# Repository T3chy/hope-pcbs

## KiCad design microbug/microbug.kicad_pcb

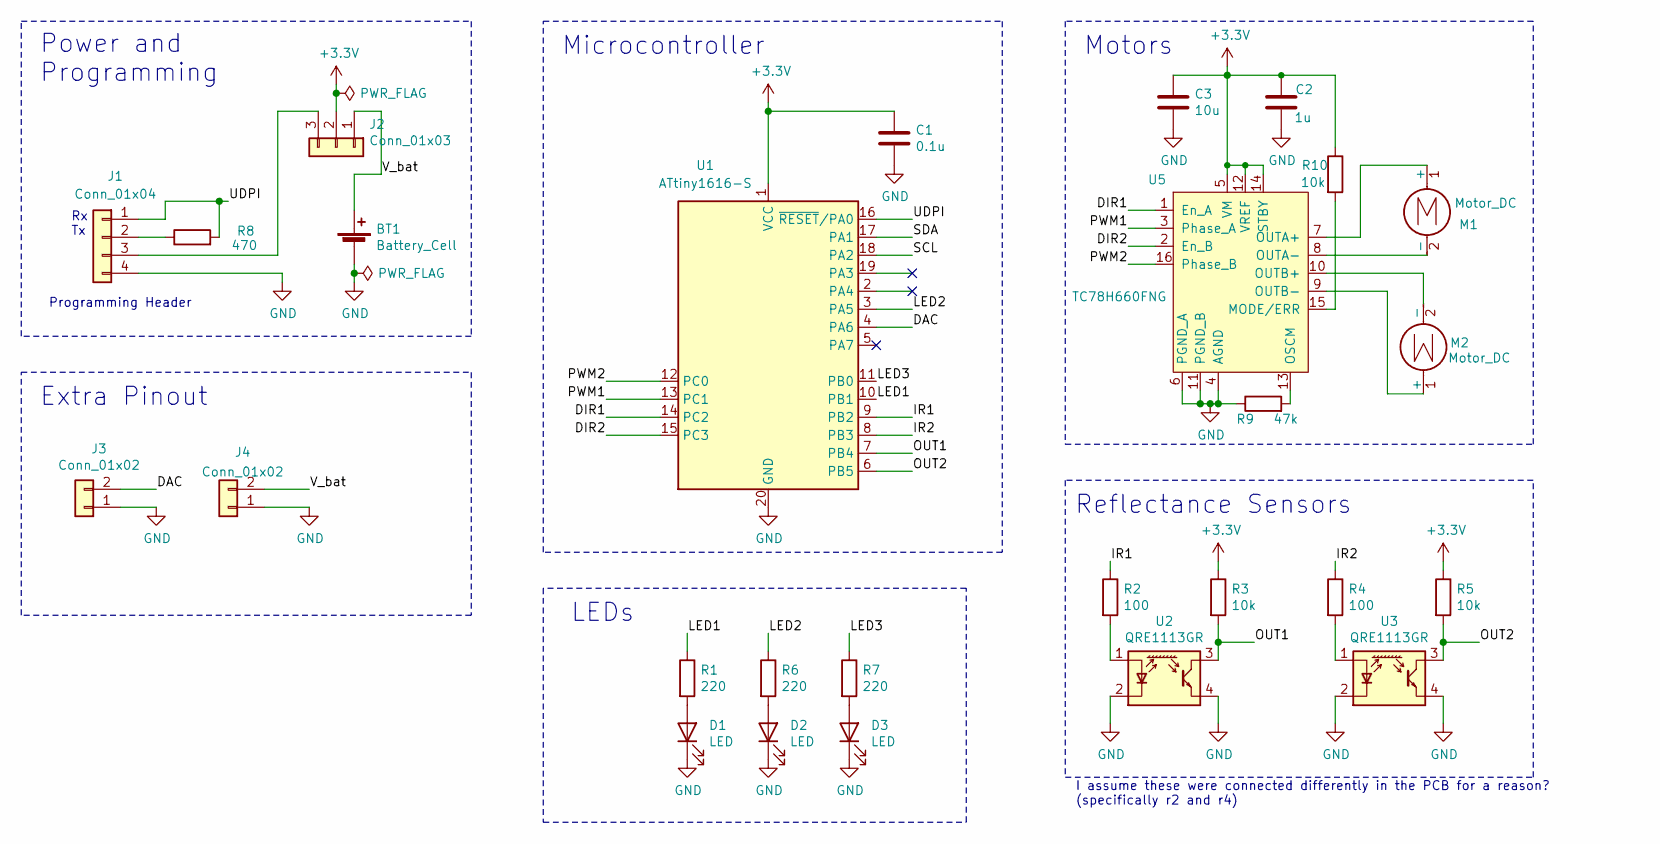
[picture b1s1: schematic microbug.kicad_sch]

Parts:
BT1: Battery_Cell; BK-883
C1: 0.1u; C_0603_1608Metric_Pad1.05x0.95mm_HandSolder
C2: 1u; C_0603_1608Metric_Pad1.05x0.95mm_HandSolder
C3: 10u; C_0603_1608Metric_Pad1.05x0.95mm_HandSolder
D1, D2, D3: LED; LED_D3.0mm
J1: Conn_01x04; PinHeader_1x04_P2.54mm_Vertical
J2: Conn_01x03; PinHeader_1x03_P2.54mm_Vertical
J3, J4: Conn_01x02; PinHeader_1x02_P2.54mm_Vertical
M1, M2: Motor_DC; micro_motor_5mm
R1, R6, R7: 220; R_0603_1608Metric_Pad1.05x0.95mm_HandSolder
R2, R4: 100; R_0603_1608Metric_Pad1.05x0.95mm_HandSolder
R3, R5, R10: 10k; R_0603_1608Metric_Pad1.05x0.95mm_HandSolder
R8: 470; R_0603_1608Metric_Pad1.05x0.95mm_HandSolder
R9: 47k; R_0603_1608Metric_Pad1.05x0.95mm_HandSolder
U1: ATtiny1616-S; SOIC-20W_7.5x12.8mm_P1.27mm
U2, U3: QRE1113GR; OnSemi_CASE100CY
U5: TC78H660FNG; TSSOP-16_4.4x5mm_P0.65mm

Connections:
+3V3: C1.1, C2.1, C3.1, J2.2, R3.1, R5.1, R10.1, U1.1 (VCC), U5.5 (VM), U5.12 (VREF), U5.14 (STBY)
/DAC: J3.2, U1.4 (PA6)
/DIR1: U1.14 (PC2), U5.1 (En_A)
/DIR2: U1.15 (PC3), U5.2 (En_B)
/IR1: R2.1, U1.9 (PB2)
/IR2: R4.1, U1.8 (PB3)
/LED1: R1.1, U1.10 (PB1)
/LED2: R6.1, U1.3 (PA5)
/LED3: R7.1, U1.11 (PB0)
/OUT1: R3.2, U1.7 (PB4), U2.3
/OUT2: R5.2, U1.6 (PB5), U3.3
/PWM1: U1.13 (PC1), U5.3 (Phase_A)
/PWM2: U1.12 (PC0), U5.16 (Phase_B)
/SCL: U1.18 (PA2)
/SDA: U1.17 (PA1)
/UDPI: J1.1, R8.2, U1.16 (~RESET/PA0)
/V_bat: BT1.1 (+), J2.1, J4.2
GND: BT1.2 (-), C1.2, C2.2, C3.2, D1.1 (K), D2.1 (K), D3.1 (K), J1.4, J3.1, J4.1, R9.1, U1.20 (GND), U2.2 (K), U2.4, U3.2 (K), U3.4, U5.4 (AGND), U5.6 (PGND_A), U5.11 (PGND_B)
unnamed: D1.2 (A), R1.2
unnamed: D2.2 (A), R6.2
unnamed: D3.2 (A), R7.2
unnamed: J1.2, R8.1
unnamed: J1.3, J2.3
unnamed: M1.1 (+), U5.7 (OUTA+)
unnamed: M1.2 (-), U5.8 (OUTA-)
unnamed: M2.1 (+), U5.9 (OUTB-)
unnamed: M2.2 (-), U5.10 (OUTB+)
unnamed: R2.2, U2.1 (A)
unnamed: R4.2, U3.1 (A)
unnamed: R9.2, U5.13 (OSCM)
unnamed: R10.2, U5.15 (MODE/ERR)

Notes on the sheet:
Power and Programming
Extra Pinout
Programming Header
Rx Tx
Microcontroller
LEDs
Reflectance Sensors
I assume these were connected differently in the PCB for a reason? (specifically r2 and r4)
Motors

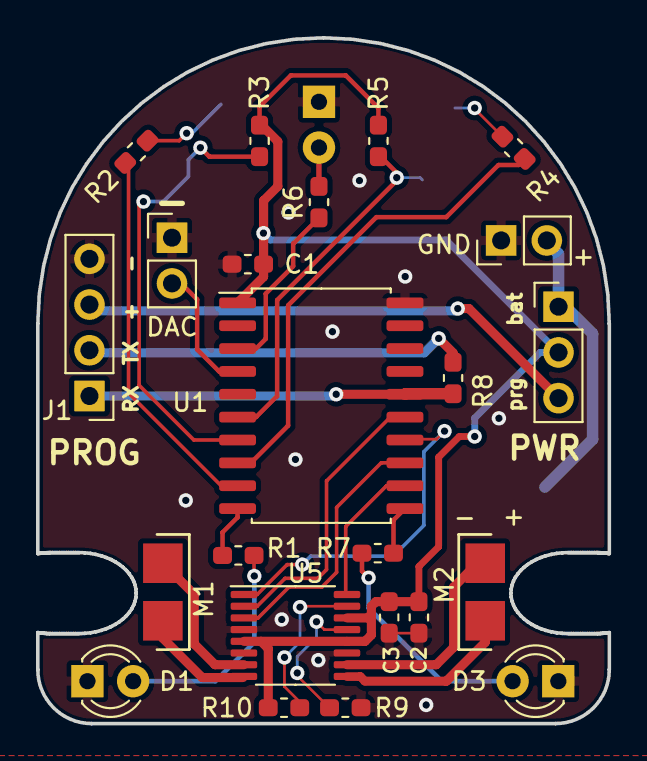
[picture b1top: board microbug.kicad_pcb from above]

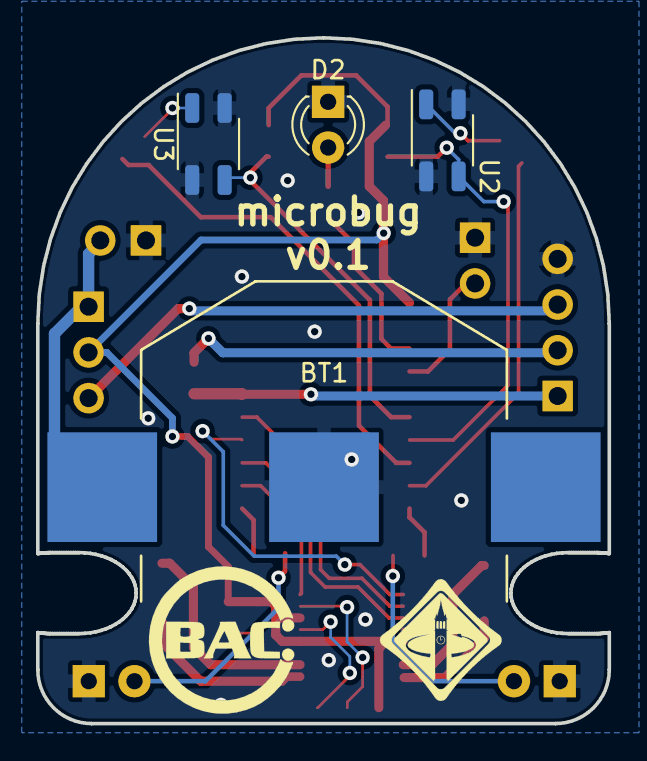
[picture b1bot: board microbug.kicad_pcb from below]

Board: 2 copper layers, 31.7 x 38.1 mm, 27 parts (4 on the bottom side), 29 nets.

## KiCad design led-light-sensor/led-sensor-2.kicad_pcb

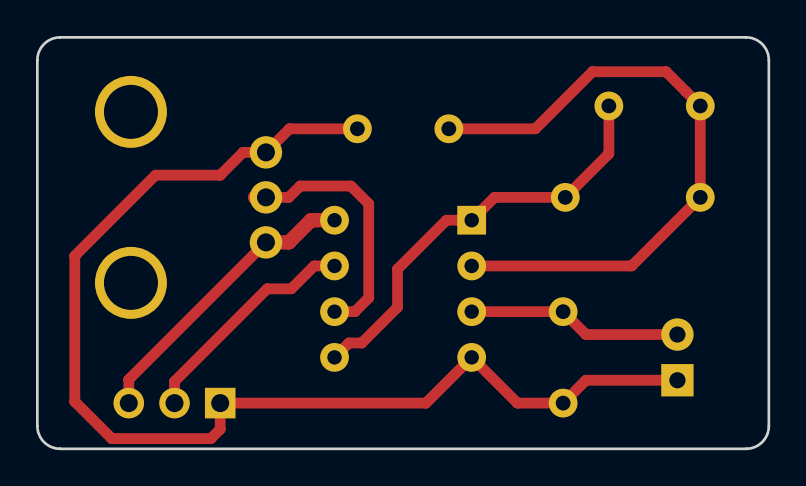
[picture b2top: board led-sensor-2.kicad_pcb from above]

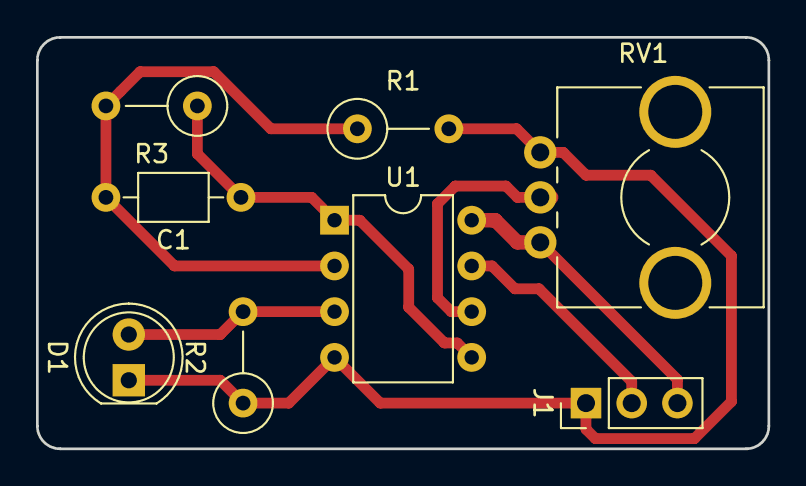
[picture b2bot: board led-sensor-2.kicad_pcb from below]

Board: 2 copper layers, 40.6 x 22.9 mm, 8 parts (8 on the bottom side), 7 nets.

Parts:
C1: 1u; C_Axial_L3.8mm_D2.6mm_P7.50mm_Horizontal
D1: LED; LED_D5.0mm
J1: CONN_01X03; Pin_Header_Straight_1x03_Pitch2.54mm
R1: 1k; R_Axial_DIN0309_L9.0mm_D3.2mm_P5.08mm_Vertical
R2: 1M; R_Axial_DIN0309_L9.0mm_D3.2mm_P5.08mm_Vertical
R3: 47k; R_Axial_DIN0309_L9.0mm_D3.2mm_P5.08mm_Vertical
RV1: POT; Potentiometer_Alps_RK09L_Sleve_Single_Horizontal
U1: LMC6482; DIP-8_W7.62mm

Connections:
+3V3: J1.3, RV1.1, U1.8
/Vout: J1.2, U1.7
GND: D1.1, J1.1, R1.2, R2.1, RV1.3, U1.4
unnamed: C1.1, R3.1, U1.1, U1.5
unnamed: C1.2, R1.1, R3.2, U1.2
unnamed: D1.2, R2.2, U1.3
unnamed: RV1.2, U1.6

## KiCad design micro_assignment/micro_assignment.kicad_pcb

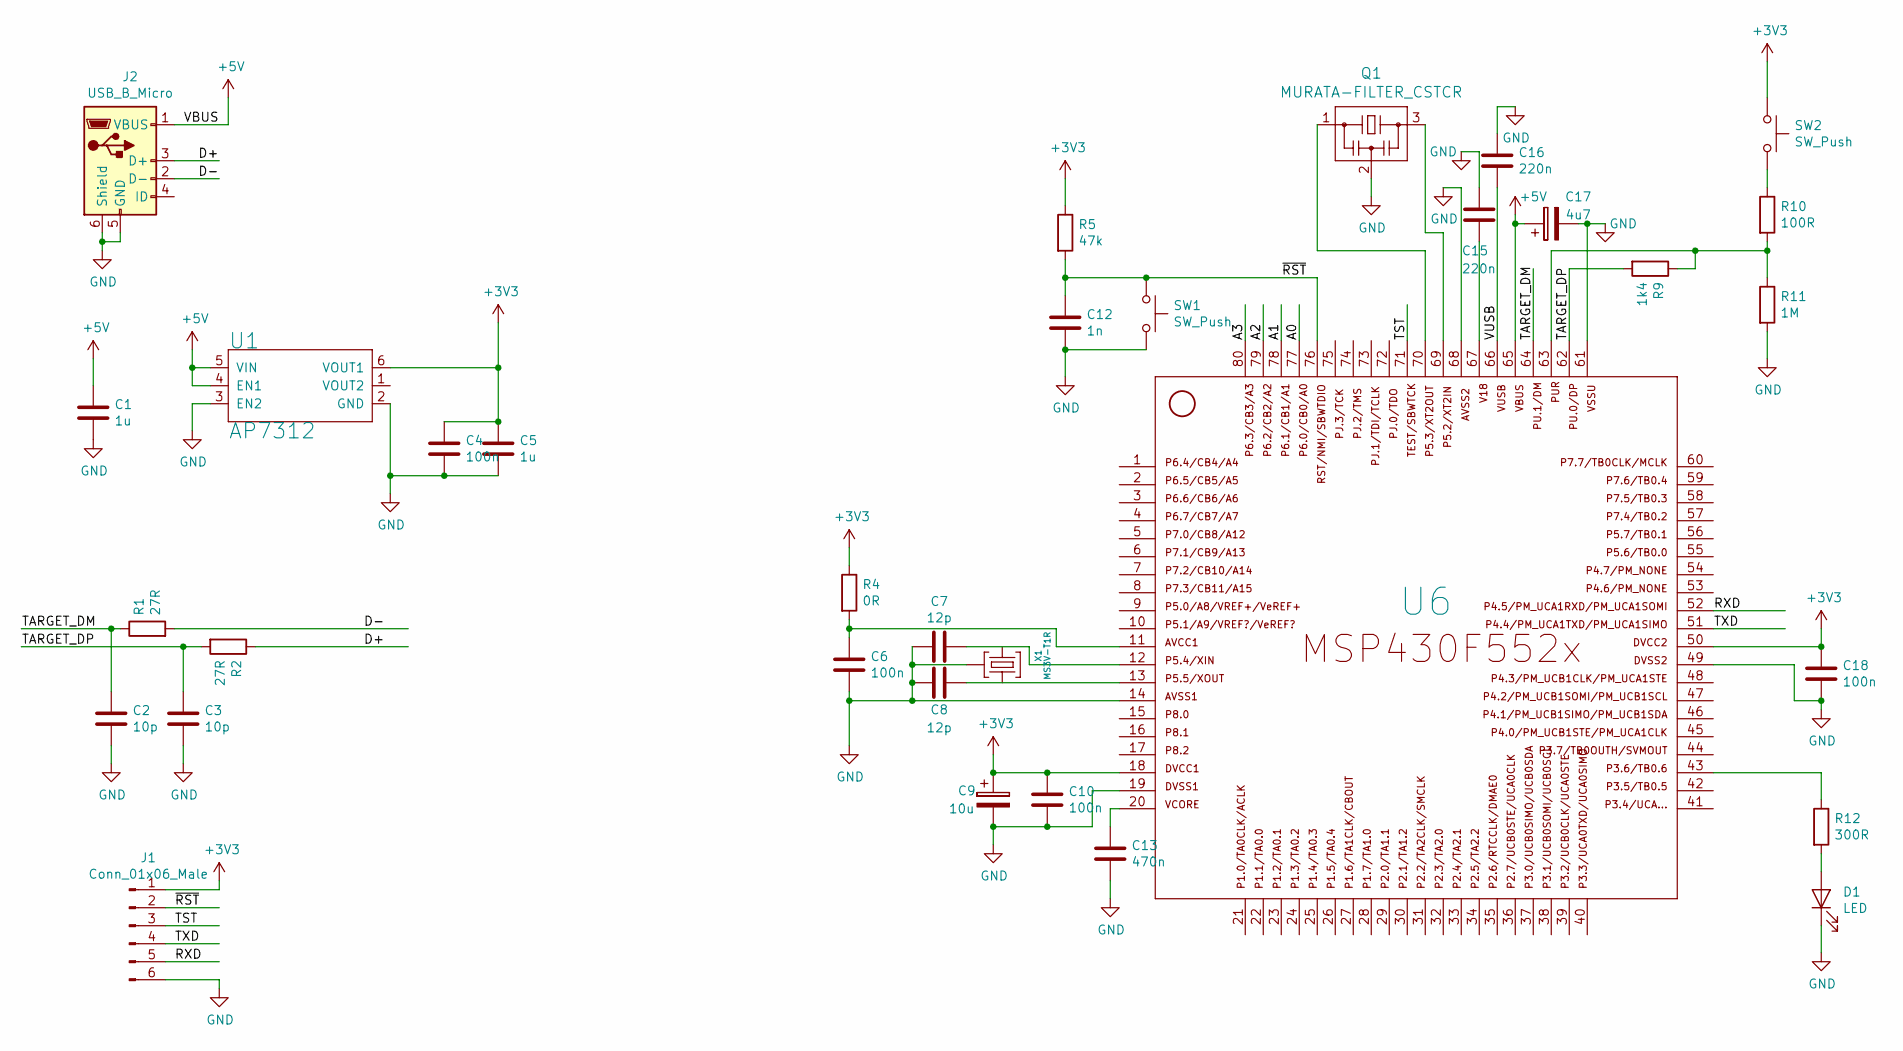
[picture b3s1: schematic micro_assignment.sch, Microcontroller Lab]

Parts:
C1, C5: 1u; C_0805_2012Metric_Pad1.15x1.40mm_HandSolder
C2, C3: 10p; C_0402_1005Metric
C4, C6, C10, C18: 100n; C_0805_2012Metric_Pad1.15x1.40mm_HandSolder
C7, C8: 12p; C_0805_2012Metric_Pad1.15x1.40mm_HandSolder
C9: 10u; 153CLV-0405
C12: 1n; C_0805_2012Metric_Pad1.15x1.40mm_HandSolder
C13: 470n; C_0805_2012Metric_Pad1.15x1.40mm_HandSolder
C15, C16: 220n; C_0805_2012Metric_Pad1.15x1.40mm_HandSolder
C17: 4u7; C_SMD_WURTH_865080540002
D1: LED; LED_0805_2012Metric_Pad1.15x1.40mm_HandSolder
J1: Conn_01x06_Male; PinHeader_1x06_P2.54mm_Vertical
J2: USB_B_Micro; USB_Micro-B_Molex-105017-0001
Q1: MURATA-FILTER_CSTCR; MURATA-CSTCR_G
R1, R2: 27R; R_0402_1005Metric
R4: 0R; R_0805_2012Metric_Pad1.15x1.40mm_HandSolder
R5: 47k; R_0805_2012Metric_Pad1.15x1.40mm_HandSolder
R9: 1k4; R_0805_2012Metric_Pad1.15x1.40mm_HandSolder
R10: 100R; R_0805_2012Metric_Pad1.15x1.40mm_HandSolder
R11: 1M; R_0805_2012Metric_Pad1.15x1.40mm_HandSolder
R12: 300R; R_0805_2012Metric_Pad1.15x1.40mm_HandSolder
SW1, SW2: SW_Push; SW_PUSH_6mm
U1: AP7312; SOT26
U6: F552X---PN80; LQFP-80_12x12mm_P0.5mm
X1: MS3V-T1R

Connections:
+3V3: C4.1, C5.1, C9.1, C10.1, C18.1, J1.1, R4.1, R5.1, SW2.1, U1.6 (VOUT1), U6.18, U6.50
+5V: C1.1, C17.1, J2.1 (VBUS), U1.4 (EN1), U1.5 (VIN), U6.65
/A0: U6.77
/A1: U6.78
/A2: U6.79
/A3: U6.80
/D+: J2.3 (D+), R2.1
/D-: J2.2 (D-), R1.2
/RXD: J1.5, U6.52
/TARGET_DM: C2.1, R1.1, U6.64
/TARGET_DP: C3.1, R2.2, R9.2, U6.62
/TST: J1.3, U6.71
/TXD: J1.4, U6.51
/VUSB: C16.2, U6.66
/~RST: C12.1, J1.2, R5.2, SW1.1, U6.76
GND: C1.2, C2.2, C3.2, C4.2, C5.2, C6.2, C7.2, C8.2, C9.2, C10.2, C12.2, C13.1, C15.1, C16.1, C17.2, C18.2, D1.1 (K), J1.6, J2.5 (GND), J2.6 (Shield), Q1.2, R11.2, SW1.2, U1.2 (GND), U1.3 (EN2), U6.14, U6.19, U6.49, U6.61, U6.68, X1.3 (GND)
unnamed: C6.1, R4.2, U6.11
unnamed: C7.1, U6.12
unnamed: C8.1, U6.13
unnamed: C13.2, U6.20
unnamed: C15.2, U6.67
unnamed: D1.2 (A), R12.2
unnamed: Q1.1, U6.70
unnamed: Q1.3, U6.69
unnamed: R10.1, SW2.2
unnamed: R9.1, R10.2, R11.1, U6.63
unnamed: R12.1, U6.43

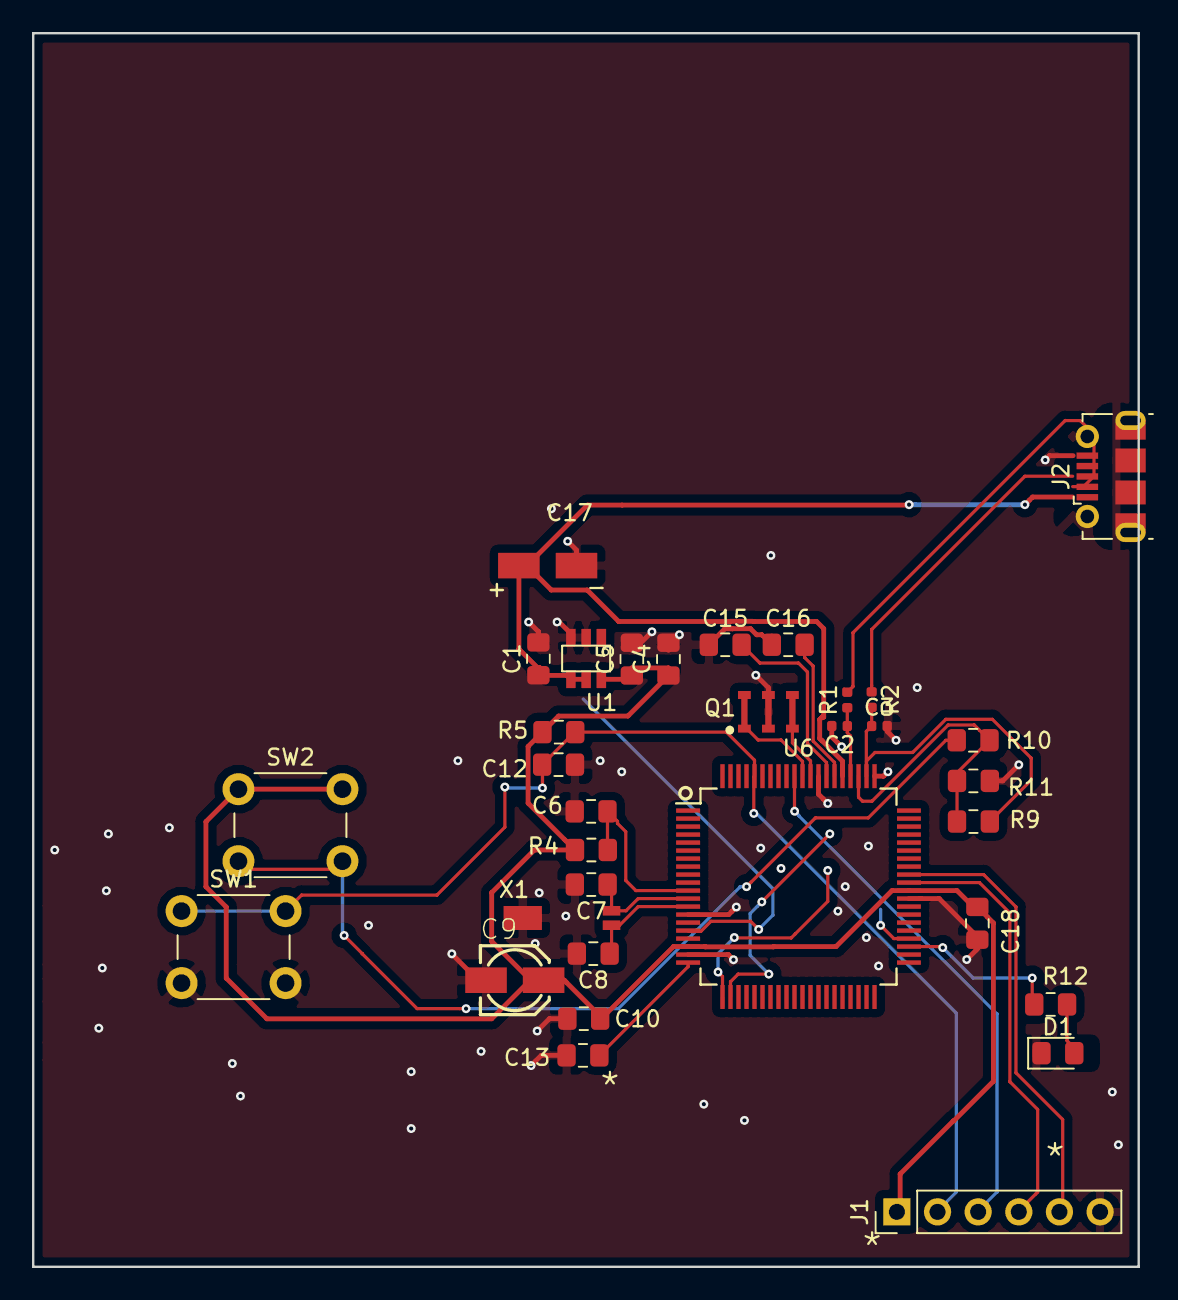
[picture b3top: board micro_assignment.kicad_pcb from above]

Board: 2 copper layers, 69.1 x 77.1 mm, 33 parts (0 on the bottom side), 23 nets.

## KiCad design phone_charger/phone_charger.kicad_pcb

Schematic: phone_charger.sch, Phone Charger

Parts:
C1: 10u (25V); C_1206_3216Metric_Pad1.42x1.75mm_HandSolder; MPN GRM319R61E106KA12D; Digi-Key_PN 490-5525-1-ND
C2: 0.1u (6.3V); C_0603_1608Metric_Pad1.05x0.95mm_HandSolder; MPN ECJ-1V1C104K
C3, C4: 22u (16V); C_0805_2012Metric_Pad1.15x1.40mm_HandSolder; MPN GRM21BR61C226ME44L; Digi-Key_PN 490-10747-1-ND
D1: LED; LED_D3.0mm; MPN 151034RS03000; Digi-Key_PN 732-11403-ND
D2: D_Schottky; D_SOD-123H; MPN CDBMT240-HF; Digi-Key_PN 641-1446-1-ND
D3: B330B; D_SMB_Handsoldering; MPN B330B-13-F; Digi-Key_PN 621-B330B-F
F1: Polyfuse; Fuse_SMD2920; MPN 0ZCF0200AF2C; Digi-Key_PN 507-1749-1-ND
J1: Conn_01x02; Pin_Header_Straight_1x02_Pitch2.54mm; MPN PREC040SAAN-RC; Digi-Key_PN S1012EC-40-ND
J2: SS-52100-001; USB_A_Female_SS-52100-001; MPN SS-52100-001; Digi-Key_PN 380-1412-ND
L1: 6.8u; L_TDK_VLF10040T-6R8N4R5; MPN VLF10040T-6R8N4R5; Digi-Key_PN 445-3561-1-ND
LOGO1: logo-symbol; bac-logo
LOGO2: logo-symbol; ieee-logo-inv
R1: 300R; R_Axial_DIN0207_L6.3mm_D2.5mm_P10.16mm_Horizontal
R2: 100k; R_0603_1608Metric_Pad1.05x0.95mm_HandSolder; MPN RMCF0603FG100K; Digi-Key_PN RMCF0603FG100KCT-ND
R3: 75k; R_0805_2012Metric_Pad1.15x1.40mm_HandSolder; MPN RMCF0805JT75K0; Digi-Key_PN RMCF0805JT75K0CT-ND
R4, R6: 50k; R_0805_2012Metric_Pad1.15x1.40mm_HandSolder; MPN MCR10ERTF4642; Digi-Key_PN RHM46.4KCHCT-ND
R5: 43k; R_0603_1608Metric_Pad1.05x0.95mm_HandSolder; MPN MCR03ERTJ433; Digi-Key_PN RHM43KCGCT-ND
R7: 0R (OPT); R_0603_1608Metric_Pad1.05x0.95mm_HandSolder
R8: 52.3k (1%); R_0603_1608Metric_Pad1.05x0.95mm_HandSolder
R9: 10k (1%); R_0805_2012Metric_Pad1.15x1.40mm_HandSolder
U1: ADP2302; SOIC-8-1EP_3.9x4.9mm_Pitch1.27mm; MPN ADP2302ARDZ-R7; Digi-Key_PN 584-ADP2302ARDZ-R7

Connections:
/D+: J2.3, R5.2, R6.1, R7.2
/D-: J2.2, R3.2, R4.1, R7.1
/SWN: C2.2, D3.1, L1.1, U1.8 (SW)
/reg_in: C1.1, D2.1, R2.1, U1.2 (VIN), U1.3 (EN)
EPAD: C1.2, C3.2, C4.2, D1.1, D3.2, J1.2, J2.4, J2.SH, R4.2, R6.2, R9.2, U1.7 (GND), U1.9 (EPAD)
unnamed: C2.1, U1.1 (BST)
unnamed: D1.2, R1.2
unnamed: D2.2, F1.1
unnamed: F1.2, J1.1
unnamed: R2.2, U1.4 (PGOOD)
unnamed: R8.2, R9.1, U1.5 (FB)
VBUS: C3.1, C4.1, J2.1, L1.2, R1.1, R3.1, R5.1, R8.1

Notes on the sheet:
Populate EITHER Apple divider resistors or 200 ohm short.

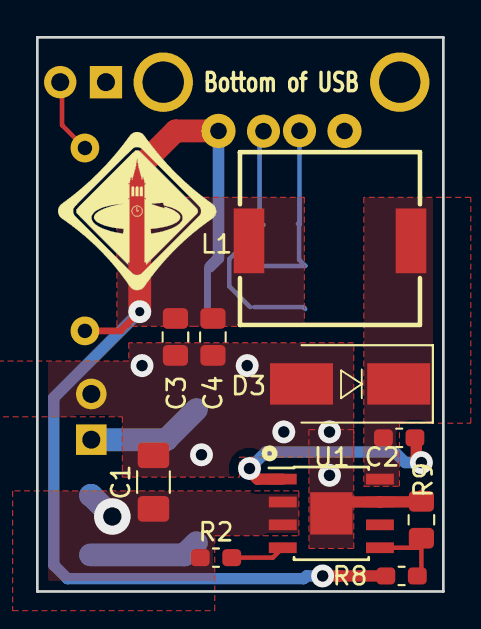
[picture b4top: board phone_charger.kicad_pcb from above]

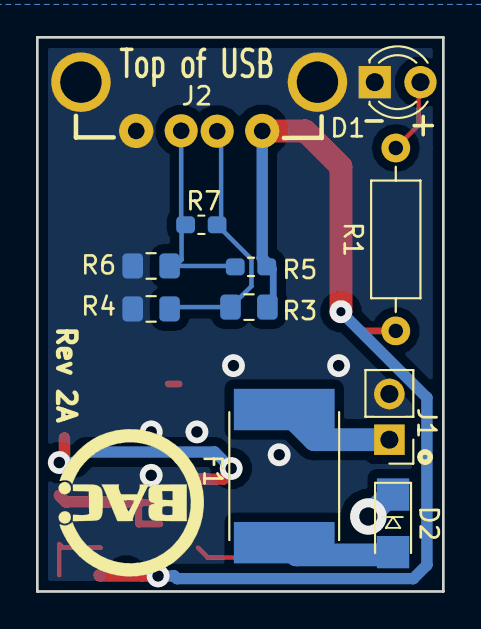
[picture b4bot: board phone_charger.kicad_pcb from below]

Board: 2 copper layers, 22.6 x 30.8 mm, 23 parts (12 on the bottom side), 12 nets.

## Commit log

2018-03-27 Add gitignore
2018-03-27 Import LED light sensor
2018-03-27 Convert to KiCad 5
2018-03-27 Update schematic
2018-03-27 Remove rescue symbols
2018-08-29 Initial kicad project phone charger project
2018-08-29 added regulator and peripherals to phone charger schematic
2018-08-29 Remove ignored files
2018-08-29 added in precision enable for phone charger
2018-08-31 Rescue symbols
2018-08-31 Add some top-level details
2018-08-31 Add values
2018-08-31 Add gate protection
2018-09-17 Phone charger symbol and schematic changes
2018-09-17 Phone charger assigned footprints
2018-09-18 placed components
2018-09-18 laid out componenets onto charger board
2018-09-18 Added charger gerbers
2018-09-18 Updated silkscreen for phone charger
2018-09-18 Move shield pin on grid and to reasonable place
2018-09-18 Fix symbol convention
2018-09-18 Place USB on grid; connect shield
2018-09-18 Point to footprint in our library
2018-09-18 Use smaller THT resistor
2018-09-18 Update PCB
2018-09-18 Fixed DRC error for phone charger
2018-09-19 Updated header footprint for charger layout
2018-09-19 Label switch node
2018-09-19 Fix VBUS trace width
2018-09-19 New phone charger gerbers
2018-09-19 Fix stuff
2018-09-19 fixed silkscreen for phone charger
2018-09-20 Remap Device libraries and remove unused symbols
2018-09-20 Add datasheet links
2018-09-20 Update fields
2018-09-20 Remove unused footprint
2018-09-20 Update DKPN and MPN fields
2018-09-20 Added silkscreens to charger board
2018-09-20 Added fb resistors to phone charger
2018-09-20 Fixed silkscreen on phone charger circuit
2018-09-20 Updated LED hole size phone charger
2018-09-20 updated schematic with silkscreen logos
2018-09-20 Change diode package to 123H
2018-09-20 Final changes to diode footprint and final gerbers
2019-01-11 Rev 2A
    - Sync SMD footprints for R's and C's from 5.0.2
    - Move diode symbol to silkscreen to indicate direction
    - Add silkscreen box around inductor
    - Indicate bottom of USB connector on silkscreen
    - Fix silkscreen component designators
2019-01-13 Update gitignore for DS_Stores
2019-01-14 Added some things to silkscreen
2019-01-14 Updated gerbs
2019-03-05 Added microcontroller lab solutions
2019-03-06 cloned microcontroller solution and fixed sch problem
2019-03-06 Updated assignment and overhauled part of solution
2019-03-07 renaming micro and making the footprints assigned for assignment version of the layout
2019-03-07 Removed net labels from microcontroller assignment schematic
2019-03-13 Reorganize schematic
2019-04-08 Update gitignore
2019-04-13 Update OtherMill design rules
2019-09-03 Update schematic annotations
2020-02-28 Initial microbug
2020-03-12 Added more LEDs, changed outline
2020-03-18 microbug bugging
2020-03-20 Organize mechanical files
2020-03-20 Forgot to commit deletion
2021-09-24 -> kicad v5.99 and added resistor for programming
2021-09-24 switched driver ic for 660
2021-09-24 added note
2021-09-24 fixed driver ic symbol name
2021-09-24 silkscreen stuff and added a via to connect ground planes
2021-09-25 fixed programming header stuff and qre111 symbol stuff
2021-09-30 pulled up mode pin
2021-09-30 pulled motor driver pin 15 up
2021-09-30 Changed out motor driver, fixed various things (for reals) (#4)
    * -> kicad v5.99 and added resistor for programming
    * switched driver ic for 660
    * added note
    * fixed driver ic symbol name
    * silkscreen stuff and added a via to connect ground planes
    * fixed programming header stuff and qre111 symbol stuff
2021-09-30 Rebuild pours, remove stray trace
2021-09-30 new layout edits, still missing logo
2021-10-01 bug gets new connector, logo silk, small changes
2021-10-14 Update silkscreen for prog header
2021-10-15 mbug logos and reorientation of extra power pins
2021-10-17 Door control board project init, made OLED symbol and FP
2021-10-18 door control wip
2021-10-18 BAC DFM clean
2021-10-20 Initial microbug fw for first rev of board
2021-10-20 door control decisions
2021-10-21 Added prog header and underside conn
2021-10-21 door control schematic update
